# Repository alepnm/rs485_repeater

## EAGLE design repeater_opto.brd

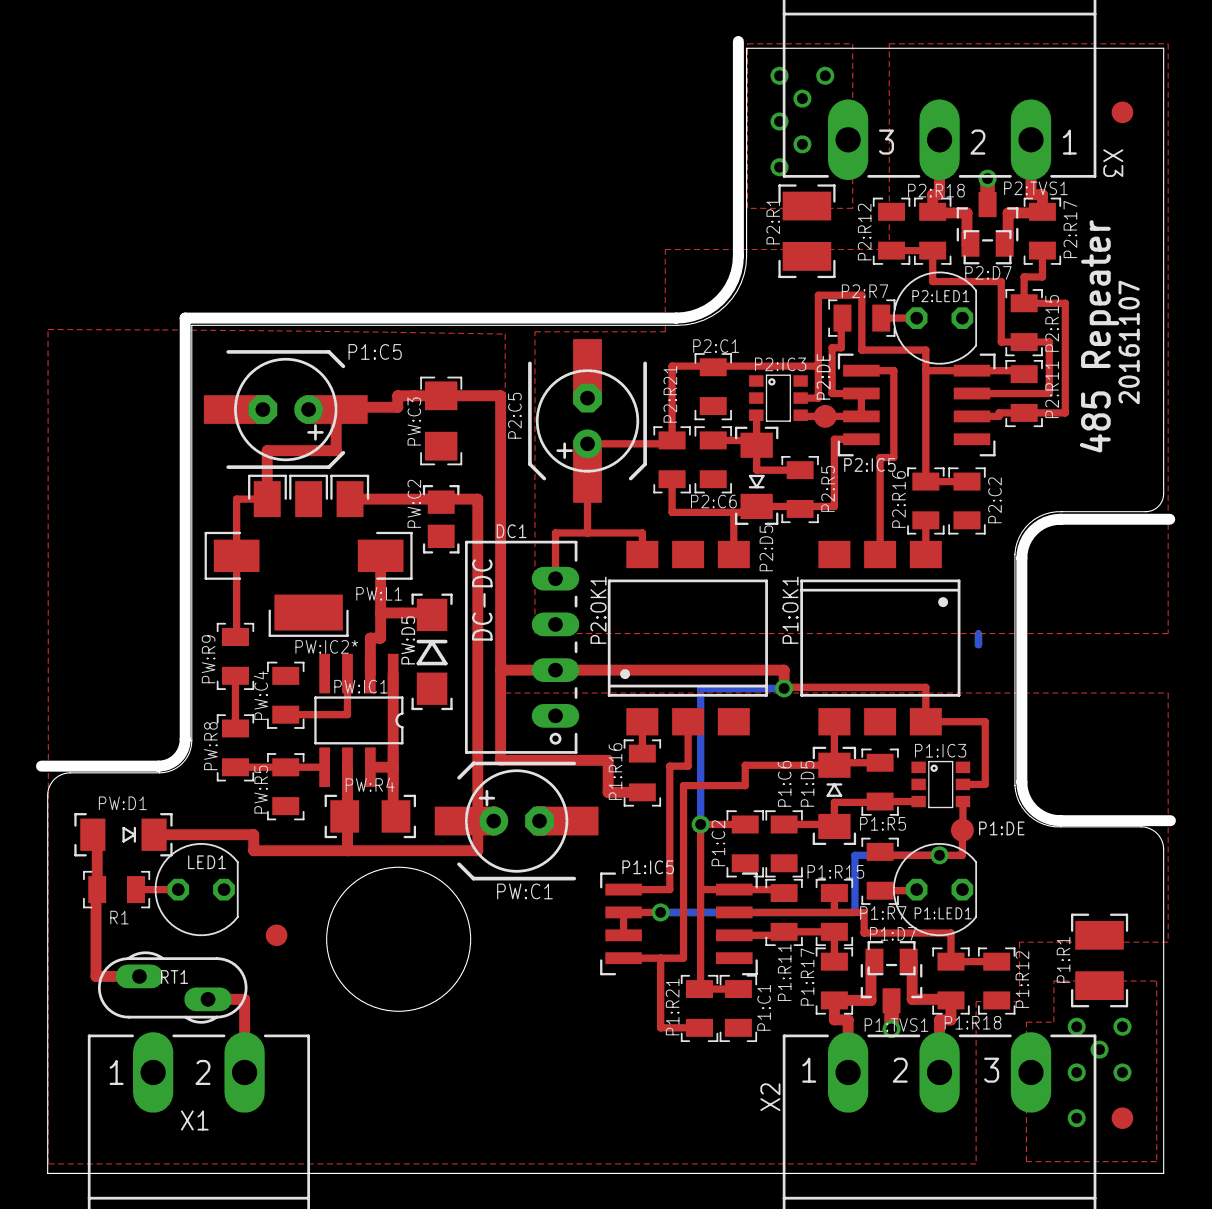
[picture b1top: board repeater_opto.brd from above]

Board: 2 copper layers, 62.7 x 62.6 mm, 69 parts (1 on the bottom side), 35 nets.

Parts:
DC1: 5V/5V; NME
LED1: Power; LED5MM
P1:C1, P1:C2, P1:C6, P2:C1, P2:C2, P2:C6: 0.1; C0805
P1:C5, P2:C5: 100x16V; SANYO-OSCON_SMD_C6
P1:C7, P2:C7: 100x16V; E2,5-6
P1:D5, P2:D5: BAS85; MINIMELF
P1:D7, P2:D7: PESD1LIN; SOD323-R
P1:DE, P2:DE: TPB1,27; B1,27
P1:IC3, P2:IC3: 74LVC2G14DBV; SOT23-6
P1:IC5, P2:IC5: MAX485CSA; ESOP-8
P1:LED1, P2:LED1: Link; LED5MM
P1:OK1, P2:OK1: H11L1MS; DIL6-SMD
P1:R1, P2:R1: 100; R1210
P1:R5, P1:R7, P2:R5, P2:R7: 10k; R0805
P1:R11, P1:R12, P2:R11, P2:R12: 4.7k; R0805
P1:R15, P2:R15: 120; R0805
P1:R16, P2:R16: 470; R0805
P1:R17, P1:R18, P2:R17, P2:R18: 10; R0805
P1:R21, P2:R21: 4k7; R0805
P1:TVS1, P2:TVS1: SM712; SOT23
PW:C1: 47x50V; SANYO-OSCON_SMD_C6
PW:C2: 10n; C0805
PW:C3: 1.0; C1206
PW:C4: 470; C0805
PW:C6: 47x50V; E2,5-6
PW:D1: BAS32; MINIMELF
PW:D5: 10MQ100; DO214BA
PW:IC1: MC34063AD; SO08
PW:IC2*: LM340-DCY; SOT223
PW:L1: 330uH; DR1030
PW:R4: 1.0; R1206
PW:R5: 4k7; R0805
PW:R8: 12k; R0805
PW:R9: 2k; R0805
R1: 4k7; R0805
RT1: 400mA; X40
SJ1: SJ
U$2: PLOKSTE_ISPJAUTA
X1: POWER; MSTBA2
X2: SIDE A; MSTBA3
X3: SIDE B; MSTBA3

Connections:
+24V: PW:D1.A, R1.1, RT1.2
GND1: DC1.1, LED1.K, P1:C1.2, P1:C2.2, P1:C5.-, P1:C6.2, P1:C7.-, P1:IC3.2, P1:IC5.5, P1:LED1.K, P1:OK1.5, P1:R1.1, P1:R12.1, PW:C1.-, PW:C2.2, PW:C3.2, PW:C4.2, PW:C6.-, PW:D5.A, PW:IC1.4, PW:IC2*.2, PW:IC2*.4, PW:R5.1, X1.1
GND2: DC1.3, P2:C1.2, P2:C2.2, P2:C5.-, P2:C6.2, P2:C7.-, P2:IC3.2, P2:IC5.5, P2:LED1.K, P2:OK1.5, P2:R1.1, P2:R12.1
unnamed: LED1.A, R1.2
unnamed: RT1.1, X1.2
unnamed: P1:R16.1, P2:OK1.1
unnamed: P1:IC5.1, P2:OK1.2
unnamed: P1:OK1.1, P2:R16.1
unnamed: P1:OK1.2, P2:IC5.1
P1:LED+: P1:DE.PP, P1:IC3.4, P1:IC5.2, P1:IC5.3, P1:R7.2
P1:N$1: P1:LED1.A, P1:R7.1
P1:N$2: P1:IC5.7, P1:R12.2, P1:R15.1, P1:R18.1
P1:N$3: P1:IC5.6, P1:R11.2, P1:R15.2, P1:R17.1
P1:N$7: P1:C6.1, P1:D5.A, P1:IC3.3, P1:R5.2
P1:RX: P1:D5.C, P1:IC5.4, P1:OK1.4, P1:R5.1, P1:R21.1
P2:LED+: P2:DE.PP, P2:IC3.4, P2:IC5.2, P2:IC5.3, P2:R7.2
P2:N$1: P2:LED1.A, P2:R7.1
P2:N$2: P2:IC5.7, P2:R12.2, P2:R15.1, P2:R18.1
P2:N$3: P2:IC5.6, P2:R11.2, P2:R15.2, P2:R17.1
P2:N$7: P2:C6.1, P2:D5.A, P2:IC3.3, P2:R5.2
P2:RX: P2:D5.C, P2:IC5.4, P2:OK1.4, P2:R5.1, P2:R21.1
PE1: P1:R1.2, P1:TVS1.3, SJ1.1, X2.3
PE2: P2:R1.2, P2:TVS1.3, SJ1.2, X3.3
PW:N$2: PW:C1.+, PW:C2.1, PW:C6.+, PW:D1.C, PW:IC1.6, PW:IC2*.1, PW:R4.1
PW:N$29: PW:IC1.1, PW:IC1.7, PW:IC1.8, PW:R4.2
PW:N$30: PW:C4.1, PW:IC1.3
PW:N$33: PW:R8.2, PW:R9.1
PW:N$34: PW:IC1.5, PW:R5.2, PW:R8.1
PW:N$35: PW:D5.C, PW:IC1.2, PW:L1.1
RS1A: P1:D7.C, P1:R17.2, P1:TVS1.2, X2.1
RS1B: P1:D7.A, P1:R18.2, P1:TVS1.1, X2.2
RS2A: P2:D7.C, P2:R17.2, P2:TVS1.2, X3.1
RS2B: P2:D7.A, P2:R18.2, P2:TVS1.1, X3.2
VCC1: DC1.2, P1:C1.1, P1:C2.1, P1:C5.+, P1:C7.+, P1:IC3.5, P1:IC5.8, P1:OK1.6, P1:R11.1, P1:R16.2, P1:R21.2, PW:C3.1, PW:IC2*.3, PW:L1.2, PW:R9.2
VCC2: DC1.4, P2:C1.1, P2:C2.1, P2:C5.+, P2:C7.+, P2:IC3.5, P2:IC5.8, P2:OK1.6, P2:R11.1, P2:R16.2, P2:R21.2

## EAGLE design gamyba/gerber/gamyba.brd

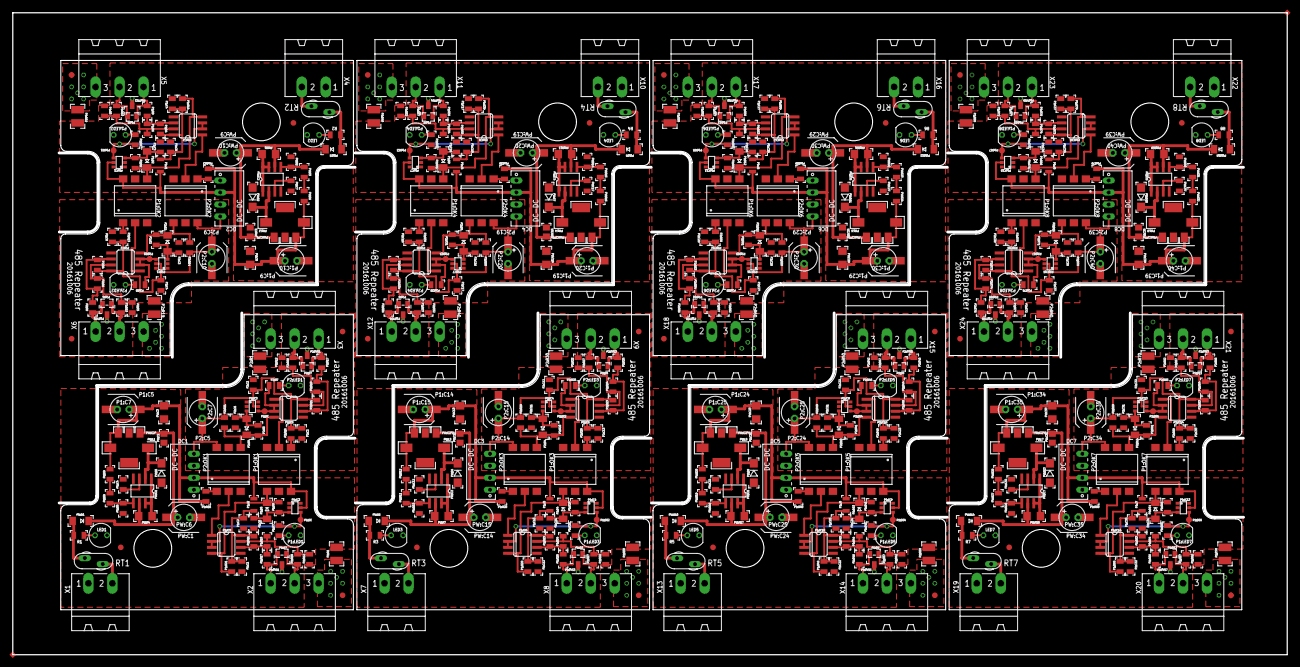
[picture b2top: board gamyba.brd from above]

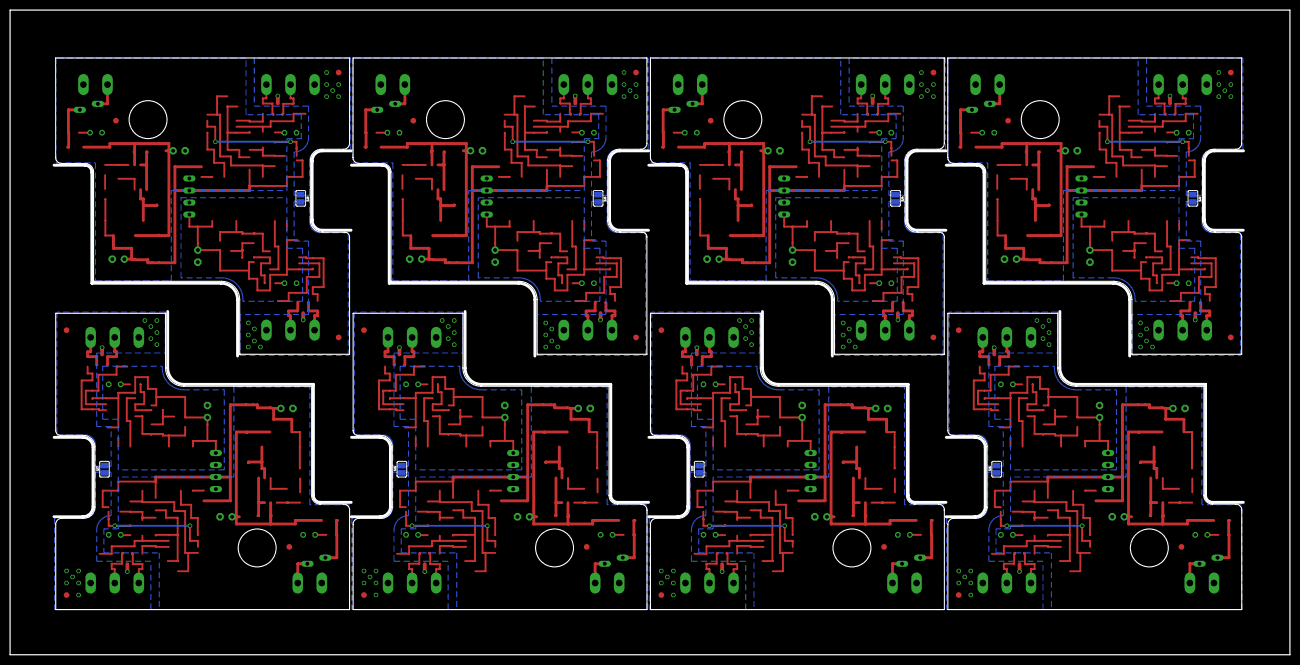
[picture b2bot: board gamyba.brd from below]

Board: 2 copper layers, 269.6 x 135.6 mm, 564 parts (8 on the bottom side), 280 nets.

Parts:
DC1, DC2, DC3, DC4, DC5, DC6, DC7, DC8: 5V/5V; NME
E$1, E$2, E$3, E$4: REF; TP2
LED1, LED2, LED3, LED4, LED5, LED6, LED7, LED8: Power; LED5MM
P1:C1, P1:C2, P1:C3, P1:C4, P1:C6, P1:C8, P1:C11, P1:C12, P1:C13, P1:C16, P1:C17, P1:C18, P1:C21, P1:C22, P1:C23, P1:C26, P1:C27, P1:C28, P1:C31, P1:C32, P1:C33, P1:C36, P1:C37, P1:C38, P2:C1, P2:C2, P2:C3, P2:C4, P2:C6, P2:C8, P2:C11, P2:C12, P2:C13, P2:C16, P2:C17, P2:C18, P2:C21, P2:C22, P2:C23, P2:C26, P2:C27, P2:C28, P2:C31, P2:C32, P2:C33, P2:C36, P2:C37, P2:C38: 0.1; C0805
P1:C5, P1:C9, P1:C14, P1:C19, P1:C24, P1:C29, P1:C34, P1:C39, P2:C5, P2:C9, P2:C14, P2:C19, P2:C24, P2:C29, P2:C34, P2:C39: 100x10V; SANYO-OSCON_SMD_C6
P1:C7, P1:C10, P1:C15, P1:C20, P1:C25, P1:C30, P1:C35, P1:C40, P2:C7, P2:C10, P2:C15, P2:C20, P2:C25, P2:C30, P2:C35, P2:C40: 100x10V; E2,5-6
P1:D1, P1:D3, P1:D6, P1:D7, P1:D9, P1:D11, P1:D13, P1:D15, P2:D1, P2:D3, P2:D6, P2:D7, P2:D9, P2:D11, P2:D13, P2:D15: PESD1LIN; SOD323-R
P1:D2, P1:D4, P1:D5, P1:D8, P1:D10, P1:D12, P1:D14, P1:D16, P2:D2, P2:D4, P2:D5, P2:D8, P2:D10, P2:D12, P2:D14, P2:D16: BAS85; MINIMELF
P1:DE, P1:DE1, P1:DE2, P1:DE3, P1:DE4, P1:DE5, P1:DE6, P1:DE7, P2:DE, P2:DE1, P2:DE2, P2:DE3, P2:DE4, P2:DE5, P2:DE6, P2:DE7: TPB1,27; B1,27
P1:IC1, P1:IC3, P1:IC4, P1:IC7, P1:IC9, P1:IC11, P1:IC13, P1:IC15, P2:IC1, P2:IC3, P2:IC4, P2:IC7, P2:IC9, P2:IC11, P2:IC13, P2:IC15: 74LVC2G14DBV; SOT23-6
P1:IC2, P1:IC5, P1:IC6, P1:IC8, P1:IC10, P1:IC12, P1:IC14, P1:IC16, P2:IC2, P2:IC5, P2:IC6, P2:IC8, P2:IC10, P2:IC12, P2:IC14, P2:IC16: MAX485CSA; SO08
P1:J1, P1:J2, P1:J3, P1:J4, P1:J5, P1:J6, P1:J7, P1:J8: 0; JUMPER_0805
P1:LED1, P1:LED2, P1:LED3, P1:LED4, P1:LED5, P1:LED6, P1:LED7, P1:LED8, P2:LED1, P2:LED2, P2:LED3, P2:LED4, P2:LED5, P2:LED6, P2:LED7, P2:LED8: Link; LED5MM
P1:OK1, P1:OK2, P1:OK3, P1:OK4, P1:OK5, P1:OK6, P1:OK7, P1:OK8, P2:OK1, P2:OK2, P2:OK3, P2:OK4, P2:OK5, P2:OK6, P2:OK7, P2:OK8: H11L1MS; DIL6-SMD
P1:R1, P1:R19, P1:R30, P1:R40, P1:R50, P1:R60, P1:R70, P1:R80, P2:R1, P2:R19, P2:R30, P2:R40, P2:R50, P2:R60, P2:R70, P2:R80: 101; R1210
P1:R2, P1:R5, P1:R7, P1:R8, P1:R20, P1:R25, P1:R31, P1:R35, P1:R41, P1:R45, P1:R51, P1:R55, P1:R61, P1:R65, P1:R71, P1:R75, P2:R2, P2:R5, P2:R7, P2:R8, P2:R20, P2:R25, P2:R31, P2:R35, P2:R41, P2:R45, P2:R51, P2:R55, P2:R61, P2:R65, P2:R71, P2:R75: 103; R0805
P1:R3, P1:R4, P1:R11, P1:R12, P1:R22, P1:R23, P1:R32, P1:R33, P1:R42, P1:R43, P1:R52, P1:R53, P1:R62, P1:R63, P1:R72, P1:R73, P2:R3, P2:R4, P2:R11, P2:R12, P2:R22, P2:R23, P2:R32, P2:R33, P2:R42, P2:R43, P2:R52, P2:R53, P2:R62, P2:R63, P2:R72, P2:R73: 202; R0805
P1:R6, P1:R15, P1:R24, P1:R34, P1:R44, P1:R54, P1:R64, P1:R74, P2:R6, P2:R15, P2:R24, P2:R34, P2:R44, P2:R54, P2:R64, P2:R74: 121; R0805
P1:R9, P1:R10, P1:R17, P1:R18, P1:R26, P1:R27, P1:R36, P1:R37, P1:R46, P1:R47, P1:R56, P1:R57, P1:R66, P1:R67, P1:R76, P1:R77, P2:R9, P2:R10, P2:R17, P2:R18, P2:R26, P2:R27, P2:R36, P2:R37, P2:R46, P2:R47, P2:R56, P2:R57, P2:R66, P2:R67, P2:R76, P2:R77: 100; R0805
P1:R13, P1:R16, P1:R28, P1:R38, P1:R48, P1:R58, P1:R68, P1:R78, P2:R13, P2:R16, P2:R28, P2:R38, P2:R48, P2:R58, P2:R68, P2:R78: 471; R0805
P1:R14, P1:R21, P1:R29, P1:R39, P1:R49, P1:R59, P1:R69, P1:R79, P2:R14, P2:R21, P2:R29, P2:R39, P2:R49, P2:R59, P2:R69, P2:R79: 472; R0805
P1:TVS1, P1:TVS2, P1:TVS3, P1:TVS4, P1:TVS5, P1:TVS6, P1:TVS7, P1:TVS8, P2:TVS1, P2:TVS2, P2:TVS3, P2:TVS4, P2:TVS5, P2:TVS6, P2:TVS7, P2:TVS8: SM712; SOT23
PW:C1, PW:C9, PW:C14, PW:C19, PW:C24, PW:C29, PW:C34, PW:C39: 47x35V; SANYO-OSCON_SMD_C6
PW:C2, PW:C5, PW:C11, PW:C16, PW:C21, PW:C26, PW:C31, PW:C36: 10n; C0805
PW:C3, PW:C8, PW:C13, PW:C18, PW:C23, PW:C28, PW:C33, PW:C38: 1.0; C1206
PW:C4, PW:C7, PW:C12, PW:C17, PW:C22, PW:C27, PW:C32, PW:C37: 470; C0805
PW:C6, PW:C10, PW:C15, PW:C20, PW:C25, PW:C30, PW:C35, PW:C40: 47x35V; E2,5-6
PW:D1, PW:D3, PW:D6, PW:D8, PW:D10, PW:D12, PW:D14, PW:D16: LL4148; MINIMELF
PW:D2, PW:D4, PW:D5, PW:D7, PW:D9, PW:D11, PW:D13, PW:D15: 10MQ100; DO214BA
PW:IC1, PW:IC2, PW:IC3, PW:IC4, PW:IC5, PW:IC6, PW:IC7, PW:IC8: MC34063AD; SO08
PW:IC2*, PW:IC2*1, PW:IC2*2, PW:IC2*3, PW:IC2*4, PW:IC2*5, PW:IC2*6, PW:IC2*7: LM340-DCY; SOT223
PW:L1, PW:L2, PW:L3, PW:L4, PW:L5, PW:L6, PW:L7, PW:L8: 330uH; DR1030
PW:R1, PW:R4, PW:R7, PW:R13, PW:R17, PW:R21, PW:R25, PW:R29: 1.0; R1206
PW:R2, PW:R5, PW:R10, PW:R14, PW:R18, PW:R22, PW:R26, PW:R30: 472; R0805
PW:R3, PW:R8, PW:R11, PW:R15, PW:R19, PW:R23, PW:R27, PW:R31: 123; R0805
PW:R6, PW:R9, PW:R12, PW:R16, PW:R20, PW:R24, PW:R28, PW:R32: 202; R0805
R1, R2, R3, R4, R5, R6, R7, R8: 472; R0805
RT1, RT2, RT3, RT4, RT5, RT6, RT7, RT8: 100mA; X40
SJ1, SJ2, SJ3, SJ4, SJ5, SJ6, SJ7, SJ8: SJ
U$1, U$2, U$3, U$4, U$5, U$6, U$7, U$8: PLOKSTE_ISPJAUTA
X1, X4, X7, X10, X13, X16, X19, X22: POWER; MSTBA2
X2, X5, X8, X11, X14, X17, X20, X23: RS1; MSTBA3
X3, X6, X9, X12, X15, X18, X21, X24: RS2; MSTBA3

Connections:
+24V: PW:D1.A, R1.1, RT1.2
+24V1: PW:D3.A, R2.1, RT2.2
+24V2: PW:D6.A, R3.1, RT3.2
+24V3: PW:D8.A, R4.1, RT4.2
+24V4: PW:D10.A, R5.1, RT5.2
+24V5: PW:D12.A, R6.1, RT6.2
+24V6: PW:D14.A, R7.1, RT7.2
+24V7: PW:D16.A, R8.1, RT8.2
GND1: DC1.1, LED1.K, P1:C1.2, P1:C2.2, P1:C5.-, P1:C6.2, P1:C7.-, P1:IC3.2, P1:IC5.5, P1:LED1.K, P1:OK1.5, P1:R1.1, P1:R12.1, PW:C1.-, PW:C2.2, PW:C3.2, PW:C4.2, PW:C6.-, PW:D5.A, PW:IC1.4, PW:IC2*.2, PW:IC2*.4, PW:R5.1, X1.1
GND2: DC1.3, P2:C1.2, P2:C2.2, P2:C5.-, P2:C6.2, P2:C7.-, P2:IC3.2, P2:IC5.5, P2:LED1.K, P2:OK1.5, P2:R1.1, P2:R12.1
GND3: DC2.3, P2:C3.2, P2:C4.2, P2:C8.2, P2:C9.-, P2:C10.-, P2:IC1.2, P2:IC2.5, P2:LED2.K, P2:OK2.5, P2:R3.1, P2:R19.1
GND4: DC2.1, LED2.K, P1:C3.2, P1:C4.2, P1:C8.2, P1:C9.-, P1:C10.-, P1:IC1.2, P1:IC2.5, P1:LED2.K, P1:OK2.5, P1:R3.1, P1:R19.1, PW:C5.2, PW:C7.2, PW:C8.2, PW:C9.-, PW:C10.-, PW:D2.A, PW:IC2.4, PW:IC2*1.2, PW:IC2*1.4, PW:R2.1, X4.1
GND5: DC3.3, P2:C11.2, P2:C12.2, P2:C13.2, P2:C14.-, P2:C15.-, P2:IC4.2, P2:IC6.5, P2:LED3.K, P2:OK3.5, P2:R22.1, P2:R30.1
GND6: DC3.1, LED3.K, P1:C11.2, P1:C12.2, P1:C13.2, P1:C14.-, P1:C15.-, P1:IC4.2, P1:IC6.5, P1:LED3.K, P1:OK3.5, P1:R22.1, P1:R30.1, PW:C11.2, PW:C12.2, PW:C13.2, PW:C14.-, PW:C15.-, PW:D4.A, PW:IC2*2.2, PW:IC2*2.4, PW:IC3.4, PW:R10.1, X7.1
GND7: DC4.3, P2:C16.2, P2:C17.2, P2:C18.2, P2:C19.-, P2:C20.-, P2:IC7.2, P2:IC8.5, P2:LED4.K, P2:OK4.5, P2:R32.1, P2:R40.1
GND8: DC4.1, LED4.K, P1:C16.2, P1:C17.2, P1:C18.2, P1:C19.-, P1:C20.-, P1:IC7.2, P1:IC8.5, P1:LED4.K, P1:OK4.5, P1:R32.1, P1:R40.1, PW:C16.2, PW:C17.2, PW:C18.2, PW:C19.-, PW:C20.-, PW:D7.A, PW:IC2*3.2, PW:IC2*3.4, PW:IC4.4, PW:R14.1, X10.1
GND9: DC5.3, P2:C21.2, P2:C22.2, P2:C23.2, P2:C24.-, P2:C25.-, P2:IC9.2, P2:IC10.5, P2:LED5.K, P2:OK5.5, P2:R42.1, P2:R50.1
GND10: DC5.1, LED5.K, P1:C21.2, P1:C22.2, P1:C23.2, P1:C24.-, P1:C25.-, P1:IC9.2, P1:IC10.5, P1:LED5.K, P1:OK5.5, P1:R42.1, P1:R50.1, PW:C21.2, PW:C22.2, PW:C23.2, PW:C24.-, PW:C25.-, PW:D9.A, PW:IC2*4.2, PW:IC2*4.4, PW:IC5.4, PW:R18.1, X13.1
GND11: DC6.3, P2:C26.2, P2:C27.2, P2:C28.2, P2:C29.-, P2:C30.-, P2:IC11.2, P2:IC12.5, P2:LED6.K, P2:OK6.5, P2:R52.1, P2:R60.1
GND12: DC6.1, LED6.K, P1:C26.2, P1:C27.2, P1:C28.2, P1:C29.-, P1:C30.-, P1:IC11.2, P1:IC12.5, P1:LED6.K, P1:OK6.5, P1:R52.1, P1:R60.1, PW:C26.2, PW:C27.2, PW:C28.2, PW:C29.-, PW:C30.-, PW:D11.A, PW:IC2*5.2, PW:IC2*5.4, PW:IC6.4, PW:R22.1, X16.1
GND13: DC7.3, P2:C31.2, P2:C32.2, P2:C33.2, P2:C34.-, P2:C35.-, P2:IC13.2, P2:IC14.5, P2:LED7.K, P2:OK7.5, P2:R62.1, P2:R70.1
GND14: DC7.1, LED7.K, P1:C31.2, P1:C32.2, P1:C33.2, P1:C34.-, P1:C35.-, P1:IC13.2, P1:IC14.5, P1:LED7.K, P1:OK7.5, P1:R62.1, P1:R70.1, PW:C31.2, PW:C32.2, PW:C33.2, PW:C34.-, PW:C35.-, PW:D13.A, PW:IC2*6.2, PW:IC2*6.4, PW:IC7.4, PW:R26.1, X19.1
GND15: DC8.3, P2:C36.2, P2:C37.2, P2:C38.2, P2:C39.-, P2:C40.-, P2:IC15.2, P2:IC16.5, P2:LED8.K, P2:OK8.5, P2:R72.1, P2:R80.1
GND16: DC8.1, LED8.K, P1:C36.2, P1:C37.2, P1:C38.2, P1:C39.-, P1:C40.-, P1:IC15.2, P1:IC16.5, P1:LED8.K, P1:OK8.5, P1:R72.1, P1:R80.1, PW:C36.2, PW:C37.2, PW:C38.2, PW:C39.-, PW:C40.-, PW:D15.A, PW:IC2*7.2, PW:IC2*7.4, PW:IC8.4, PW:R30.1, X22.1
unnamed: LED1.A, R1.2
unnamed: RT1.1, X1.2
unnamed: P1:R13.1, P2:OK2.1
unnamed: P1:OK2.1, P2:R13.1
unnamed: P1:IC2.1, P2:OK2.2
unnamed: P1:OK2.2, P2:IC2.1
unnamed: RT2.1, X4.2
unnamed: LED2.A, R2.2
unnamed: P1:R28.1, P2:OK3.1
unnamed: P1:OK3.1, P2:R28.1
unnamed: P1:IC6.1, P2:OK3.2
unnamed: P1:R16.1, P2:OK1.1
unnamed: P1:IC5.1, P2:OK1.2
unnamed: P1:OK1.1, P2:R16.1
unnamed: P1:OK1.2, P2:IC5.1
unnamed: P1:OK3.2, P2:IC6.1
unnamed: RT3.1, X7.2
unnamed: LED3.A, R3.2
unnamed: P1:R38.1, P2:OK4.1
unnamed: P1:OK4.1, P2:R38.1
unnamed: P1:IC8.1, P2:OK4.2
unnamed: P1:OK4.2, P2:IC8.1
unnamed: RT4.1, X10.2
unnamed: LED4.A, R4.2
unnamed: P1:R48.1, P2:OK5.1
unnamed: P1:OK5.1, P2:R48.1
unnamed: P1:IC10.1, P2:OK5.2
unnamed: P1:OK5.2, P2:IC10.1
unnamed: RT5.1, X13.2
unnamed: LED5.A, R5.2
unnamed: P1:R58.1, P2:OK6.1
unnamed: P1:OK6.1, P2:R58.1
unnamed: P1:IC12.1, P2:OK6.2
unnamed: P1:OK6.2, P2:IC12.1
unnamed: RT6.1, X16.2
unnamed: LED6.A, R6.2
unnamed: P1:R68.1, P2:OK7.1
unnamed: P1:OK7.1, P2:R68.1
unnamed: P1:IC14.1, P2:OK7.2
unnamed: P1:OK7.2, P2:IC14.1
unnamed: RT7.1, X19.2
unnamed: LED7.A, R7.2
unnamed: P1:R78.1, P2:OK8.1
unnamed: P1:OK8.1, P2:R78.1
unnamed: P1:IC16.1, P2:OK8.2
unnamed: P1:OK8.2, P2:IC16.1
unnamed: RT8.1, X22.2
unnamed: LED8.A, R8.2
P1:LED+: P1:DE.PP, P1:IC3.4, P1:IC5.2, P1:IC5.3, P1:R7.2
P1:LED+1: P1:DE1.PP, P1:IC1.4, P1:IC2.2, P1:IC2.3, P1:R8.2
P1:LED+2: P1:DE2.PP, P1:IC4.4, P1:IC6.2, P1:IC6.3, P1:R25.2
P1:LED+3: P1:DE3.PP, P1:IC7.4, P1:IC8.2, P1:IC8.3, P1:R35.2
P1:LED+4: P1:DE4.PP, P1:IC9.4, P1:IC10.2, P1:IC10.3, P1:R45.2
P1:LED+5: P1:DE5.PP, P1:IC11.4, P1:IC12.2, P1:IC12.3, P1:R55.2
P1:LED+6: P1:DE6.PP, P1:IC13.4, P1:IC14.2, P1:IC14.3, P1:R65.2
P1:LED+7: P1:DE7.PP, P1:IC15.4, P1:IC16.2, P1:IC16.3, P1:R75.2
P1:N$1: P1:LED1.A, P1:R7.1
P1:N$2: P1:IC5.7, P1:R12.2, P1:R15.1, P1:R18.1
P1:N$3: P1:IC5.6, P1:R11.2, P1:R15.2, P1:R17.1
P1:N$4: P1:C3.1, P1:D2.A, P1:IC1.3, P1:R2.2
P1:N$5: P1:IC2.7, P1:R3.2, P1:R6.1, P1:R10.1
P1:N$6: P1:IC2.6, P1:R4.2, P1:R6.2, P1:R9.1
P1:N$7: P1:C6.1, P1:D5.A, P1:IC3.3, P1:R5.2
P1:N$8: P1:LED2.A, P1:R8.1
P1:N$9: P1:C11.1, P1:D4.A, P1:IC4.3, P1:R20.2
P1:N$10: P1:IC6.7, P1:R22.2, P1:R24.1, P1:R27.1
P1:N$11: P1:IC6.6, P1:R23.2, P1:R24.2, P1:R26.1
P1:N$12: P1:LED3.A, P1:R25.1
P1:N$13: P1:C16.1, P1:D8.A, P1:IC7.3, P1:R31.2
P1:N$14: P1:IC8.7, P1:R32.2, P1:R34.1, P1:R37.1
P1:N$15: P1:IC8.6, P1:R33.2, P1:R34.2, P1:R36.1
P1:N$16: P1:LED4.A, P1:R35.1
P1:N$17: P1:C21.1, P1:D10.A, P1:IC9.3, P1:R41.2
P1:N$18: P1:IC10.7, P1:R42.2, P1:R44.1, P1:R47.1
P1:N$19: P1:IC10.6, P1:R43.2, P1:R44.2, P1:R46.1
P1:N$20: P1:LED5.A, P1:R45.1
P1:N$21: P1:C26.1, P1:D12.A, P1:IC11.3, P1:R51.2
P1:N$22: P1:IC12.7, P1:R52.2, P1:R54.1, P1:R57.1
P1:N$23: P1:IC12.6, P1:R53.2, P1:R54.2, P1:R56.1
P1:N$24: P1:LED6.A, P1:R55.1
P1:N$25: P1:C31.1, P1:D14.A, P1:IC13.3, P1:R61.2
P1:N$26: P1:IC14.7, P1:R62.2, P1:R64.1, P1:R67.1
P1:N$27: P1:IC14.6, P1:R63.2, P1:R64.2, P1:R66.1
P1:N$28: P1:LED7.A, P1:R65.1
P1:N$29: P1:C36.1, P1:D16.A, P1:IC15.3, P1:R71.2
P1:N$30: P1:IC16.7, P1:R72.2, P1:R74.1, P1:R77.1
P1:N$31: P1:IC16.6, P1:R73.2, P1:R74.2, P1:R76.1
P1:N$32: P1:LED8.A, P1:R75.1
P1:RX: P1:D5.C, P1:IC5.4, P1:OK1.4, P1:R5.1, P1:R21.1
P1:RX1: P1:D2.C, P1:IC2.4, P1:OK2.4, P1:R2.1, P1:R14.1
P1:RX2: P1:D4.C, P1:IC6.4, P1:OK3.4, P1:R20.1, P1:R29.1
P1:RX3: P1:D8.C, P1:IC8.4, P1:OK4.4, P1:R31.1, P1:R39.1
P1:RX4: P1:D10.C, P1:IC10.4, P1:OK5.4, P1:R41.1, P1:R49.1
P1:RX5: P1:D12.C, P1:IC12.4, P1:OK6.4, P1:R51.1, P1:R59.1
P1:RX6: P1:D14.C, P1:IC14.4, P1:OK7.4, P1:R61.1, P1:R69.1
P1:RX7: P1:D16.C, P1:IC16.4, P1:OK8.4, P1:R71.1, P1:R79.1
P2:LED+: P2:DE.PP, P2:IC3.4, P2:IC5.2, P2:IC5.3, P2:R7.2
P2:LED+1: P2:DE1.PP, P2:IC1.4, P2:IC2.2, P2:IC2.3, P2:R8.2
P2:LED+2: P2:DE2.PP, P2:IC4.4, P2:IC6.2, P2:IC6.3, P2:R25.2
P2:LED+3: P2:DE3.PP, P2:IC7.4, P2:IC8.2, P2:IC8.3, P2:R35.2
P2:LED+4: P2:DE4.PP, P2:IC9.4, P2:IC10.2, P2:IC10.3, P2:R45.2
P2:LED+5: P2:DE5.PP, P2:IC11.4, P2:IC12.2, P2:IC12.3, P2:R55.2
P2:LED+6: P2:DE6.PP, P2:IC13.4, P2:IC14.2, P2:IC14.3, P2:R65.2
P2:LED+7: P2:DE7.PP, P2:IC15.4, P2:IC16.2, P2:IC16.3, P2:R75.2
P2:N$1: P2:LED1.A, P2:R7.1
P2:N$2: P2:IC5.7, P2:R12.2, P2:R15.1, P2:R18.1
P2:N$3: P2:IC5.6, P2:R11.2, P2:R15.2, P2:R17.1
P2:N$4: P2:C3.1, P2:D2.A, P2:IC1.3, P2:R2.2
P2:N$5: P2:IC2.7, P2:R3.2, P2:R6.1, P2:R10.1
P2:N$6: P2:IC2.6, P2:R4.2, P2:R6.2, P2:R9.1
P2:N$7: P2:C6.1, P2:D5.A, P2:IC3.3, P2:R5.2
P2:N$8: P2:LED2.A, P2:R8.1
P2:N$9: P2:C11.1, P2:D4.A, P2:IC4.3, P2:R20.2
P2:N$10: P2:IC6.7, P2:R22.2, P2:R24.1, P2:R27.1
P2:N$11: P2:IC6.6, P2:R23.2, P2:R24.2, P2:R26.1
P2:N$12: P2:LED3.A, P2:R25.1
P2:N$13: P2:C16.1, P2:D8.A, P2:IC7.3, P2:R31.2
P2:N$14: P2:IC8.7, P2:R32.2, P2:R34.1, P2:R37.1
P2:N$15: P2:IC8.6, P2:R33.2, P2:R34.2, P2:R36.1
P2:N$16: P2:LED4.A, P2:R35.1
P2:N$17: P2:C21.1, P2:D10.A, P2:IC9.3, P2:R41.2
P2:N$18: P2:IC10.7, P2:R42.2, P2:R44.1, P2:R47.1
P2:N$19: P2:IC10.6, P2:R43.2, P2:R44.2, P2:R46.1
P2:N$20: P2:LED5.A, P2:R45.1
P2:N$21: P2:C26.1, P2:D12.A, P2:IC11.3, P2:R51.2
P2:N$22: P2:IC12.7, P2:R52.2, P2:R54.1, P2:R57.1
P2:N$23: P2:IC12.6, P2:R53.2, P2:R54.2, P2:R56.1
P2:N$24: P2:LED6.A, P2:R55.1
P2:N$25: P2:C31.1, P2:D14.A, P2:IC13.3, P2:R61.2
P2:N$26: P2:IC14.7, P2:R62.2, P2:R64.1, P2:R67.1
P2:N$27: P2:IC14.6, P2:R63.2, P2:R64.2, P2:R66.1
P2:N$28: P2:LED7.A, P2:R65.1
P2:N$29: P2:C36.1, P2:D16.A, P2:IC15.3, P2:R71.2
P2:N$30: P2:IC16.7, P2:R72.2, P2:R74.1, P2:R77.1
P2:N$31: P2:IC16.6, P2:R73.2, P2:R74.2, P2:R76.1
P2:N$32: P2:LED8.A, P2:R75.1
P2:RX: P2:D5.C, P2:IC5.4, P2:OK1.4, P2:R5.1, P2:R21.1
P2:RX1: P2:D2.C, P2:IC2.4, P2:OK2.4, P2:R2.1, P2:R14.1
P2:RX2: P2:D4.C, P2:IC6.4, P2:OK3.4, P2:R20.1, P2:R29.1
P2:RX3: P2:D8.C, P2:IC8.4, P2:OK4.4, P2:R31.1, P2:R39.1
P2:RX4: P2:D10.C, P2:IC10.4, P2:OK5.4, P2:R41.1, P2:R49.1
P2:RX5: P2:D12.C, P2:IC12.4, P2:OK6.4, P2:R51.1, P2:R59.1
P2:RX6: P2:D14.C, P2:IC14.4, P2:OK7.4, P2:R61.1, P2:R69.1
P2:RX7: P2:D16.C, P2:IC16.4, P2:OK8.4, P2:R71.1, P2:R79.1
PE1: P1:R1.2, P1:TVS1.3, SJ1.1, X2.3
PE2: P2:R1.2, P2:TVS1.3, SJ1.2, X3.3
PE3: P1:R19.2, P1:TVS2.3, SJ2.1, X5.3
PE4: P2:R19.2, P2:TVS2.3, SJ2.2, X6.3
PE5: P1:R30.2, P1:TVS3.3, SJ3.1, X8.3
PE6: P2:R30.2, P2:TVS3.3, SJ3.2, X9.3
PE7: P1:R40.2, P1:TVS4.3, SJ4.1, X11.3
PE8: P2:R40.2, P2:TVS4.3, SJ4.2, X12.3
PE9: P1:R50.2, P1:TVS5.3, SJ5.1, X14.3
PE10: P2:R50.2, P2:TVS5.3, SJ5.2, X15.3
PE11: P1:R60.2, P1:TVS6.3, SJ6.1, X17.3
PE12: P2:R60.2, P2:TVS6.3, SJ6.2, X18.3
PE13: P1:R70.2, P1:TVS7.3, SJ7.1, X20.3
PE14: P2:R70.2, P2:TVS7.3, SJ7.2, X21.3
PE15: P1:R80.2, P1:TVS8.3, SJ8.1, X23.3
PE16: P2:R80.2, P2:TVS8.3, SJ8.2, X24.3
PW:N$1: PW:IC2.1, PW:IC2.7, PW:IC2.8, PW:R1.2
PW:N$2: PW:C1.+, PW:C2.1, PW:C6.+, PW:D1.C, PW:IC1.6, PW:IC2*.1, PW:R4.1
PW:N$3: PW:IC2.5, PW:R2.2, PW:R3.1
PW:N$4: PW:C7.1, PW:IC2.3
PW:N$5: PW:D2.C, PW:IC2.2, PW:L2.1
PW:N$6: PW:R3.2, PW:R6.1
PW:N$7: PW:C5.1, PW:C9.+, PW:C10.+, PW:D3.C, PW:IC2.6, PW:IC2*1.1, PW:R1.1
PW:N$8: PW:IC3.1, PW:IC3.7, PW:IC3.8, PW:R7.2
PW:N$9: PW:IC3.5, PW:R10.2, PW:R11.1
PW:N$10: PW:C12.1, PW:IC3.3
PW:N$11: PW:D4.C, PW:IC3.2, PW:L3.1
PW:N$12: PW:R11.2, PW:R12.1
PW:N$13: PW:C11.1, PW:C14.+, PW:C15.+, PW:D6.C, PW:IC2*2.1, PW:IC3.6, PW:R7.1
PW:N$14: PW:IC4.1, PW:IC4.7, PW:IC4.8, PW:R13.2
PW:N$15: PW:IC4.5, PW:R14.2, PW:R15.1
PW:N$16: PW:C17.1, PW:IC4.3
PW:N$17: PW:D7.C, PW:IC4.2, PW:L4.1
PW:N$18: PW:R15.2, PW:R16.1
PW:N$19: PW:C16.1, PW:C19.+, PW:C20.+, PW:D8.C, PW:IC2*3.1, PW:IC4.6, PW:R13.1
PW:N$20: PW:IC5.1, PW:IC5.7, PW:IC5.8, PW:R17.2
PW:N$21: PW:IC5.5, PW:R18.2, PW:R19.1
PW:N$22: PW:C22.1, PW:IC5.3
PW:N$23: PW:D9.C, PW:IC5.2, PW:L5.1
PW:N$24: PW:R19.2, PW:R20.1
PW:N$25: PW:C21.1, PW:C24.+, PW:C25.+, PW:D10.C, PW:IC2*4.1, PW:IC5.6, PW:R17.1
PW:N$26: PW:IC6.1, PW:IC6.7, PW:IC6.8, PW:R21.2
PW:N$27: PW:IC6.5, PW:R22.2, PW:R23.1
PW:N$28: PW:C27.1, PW:IC6.3
PW:N$29: PW:IC1.1, PW:IC1.7, PW:IC1.8, PW:R4.2
PW:N$30: PW:C4.1, PW:IC1.3
PW:N$31: PW:D11.C, PW:IC6.2, PW:L6.1
PW:N$32: PW:R23.2, PW:R24.1
PW:N$33: PW:R8.2, PW:R9.1
PW:N$34: PW:IC1.5, PW:R5.2, PW:R8.1
PW:N$35: PW:D5.C, PW:IC1.2, PW:L1.1
PW:N$36: PW:C26.1, PW:C29.+, PW:C30.+, PW:D12.C, PW:IC2*5.1, PW:IC6.6, PW:R21.1
PW:N$37: PW:IC7.1, PW:IC7.7, PW:IC7.8, PW:R25.2
PW:N$38: PW:IC7.5, PW:R26.2, PW:R27.1
PW:N$39: PW:C32.1, PW:IC7.3
PW:N$40: PW:D13.C, PW:IC7.2, PW:L7.1
PW:N$41: PW:R27.2, PW:R28.1
PW:N$42: PW:C31.1, PW:C34.+, PW:C35.+, PW:D14.C, PW:IC2*6.1, PW:IC7.6, PW:R25.1
PW:N$43: PW:IC8.1, PW:IC8.7, PW:IC8.8, PW:R29.2
PW:N$44: PW:IC8.5, PW:R30.2, PW:R31.1
PW:N$45: PW:C37.1, PW:IC8.3
PW:N$46: PW:D15.C, PW:IC8.2, PW:L8.1
PW:N$47: PW:R31.2, PW:R32.1
PW:N$48: PW:C36.1, PW:C39.+, PW:C40.+, PW:D16.C, PW:IC2*7.1, PW:IC8.6, PW:R29.1
RS1A: P1:D7.C, P1:R17.2, P1:TVS1.2, X2.1
RS1A1: P1:D1.C, P1:R9.2, P1:TVS2.2, X5.1
RS1A2: P1:D3.C, P1:R26.2, P1:TVS3.2, X8.1
RS1A3: P1:D6.C, P1:R36.2, P1:TVS4.2, X11.1
RS1A4: P1:D9.C, P1:R46.2, P1:TVS5.2, X14.1
RS1A5: P1:D11.C, P1:R56.2, P1:TVS6.2, X17.1
RS1A6: P1:D13.C, P1:R66.2, P1:TVS7.2, X20.1
RS1A7: P1:D15.C, P1:R76.2, P1:TVS8.2, X23.1
RS1B: P1:D7.A, P1:R18.2, P1:TVS1.1, X2.2
RS1B1: P1:D1.A, P1:R10.2, P1:TVS2.1, X5.2
RS1B2: P1:D3.A, P1:R27.2, P1:TVS3.1, X8.2
RS1B3: P1:D6.A, P1:R37.2, P1:TVS4.1, X11.2
RS1B4: P1:D9.A, P1:R47.2, P1:TVS5.1, X14.2
RS1B5: P1:D11.A, P1:R57.2, P1:TVS6.1, X17.2
RS1B6: P1:D13.A, P1:R67.2, P1:TVS7.1, X20.2
RS1B7: P1:D15.A, P1:R77.2, P1:TVS8.1, X23.2
RS2A: P2:D7.C, P2:R17.2, P2:TVS1.2, X3.1
RS2A1: P2:D1.C, P2:R9.2, P2:TVS2.2, X6.1
RS2A2: P2:D3.C, P2:R26.2, P2:TVS3.2, X9.1
RS2A3: P2:D6.C, P2:R36.2, P2:TVS4.2, X12.1
RS2A4: P2:D9.C, P2:R46.2, P2:TVS5.2, X15.1
RS2A5: P2:D11.C, P2:R56.2, P2:TVS6.2, X18.1
RS2A6: P2:D13.C, P2:R66.2, P2:TVS7.2, X21.1
RS2A7: P2:D15.C, P2:R76.2, P2:TVS8.2, X24.1
RS2B: P2:D7.A, P2:R18.2, P2:TVS1.1, X3.2
RS2B1: P2:D1.A, P2:R10.2, P2:TVS2.1, X6.2
RS2B2: P2:D3.A, P2:R27.2, P2:TVS3.1, X9.2
RS2B3: P2:D6.A, P2:R37.2, P2:TVS4.1, X12.2
RS2B4: P2:D9.A, P2:R47.2, P2:TVS5.1, X15.2
RS2B5: P2:D11.A, P2:R57.2, P2:TVS6.1, X18.2
RS2B6: P2:D13.A, P2:R67.2, P2:TVS7.1, X21.2
RS2B7: P2:D15.A, P2:R77.2, P2:TVS8.1, X24.2
VCC1: DC1.2, P1:C1.1, P1:C2.1, P1:C5.+, P1:C7.+, P1:IC3.5, P1:IC5.8, P1:J2.1, P1:J2.2, P1:OK1.6, P1:R11.1, P1:R16.2, P1:R21.2, PW:C3.1, PW:IC2*.3, PW:L1.2, PW:R9.2
VCC2: DC1.4, P2:C1.1, P2:C2.1, P2:C5.+, P2:C7.+, P2:IC3.5, P2:IC5.8, P2:OK1.6, P2:R11.1, P2:R16.2, P2:R21.2
VCC3: DC2.2, P1:C4.1, P1:C8.1, P1:C9.+, P1:C10.+, P1:IC1.5, P1:IC2.8, P1:J1.1, P1:J1.2, P1:OK2.6, P1:R4.1, P1:R13.2, P1:R14.2, PW:C8.1, PW:IC2*1.3, PW:L2.2, PW:R6.2
VCC4: DC2.4, P2:C4.1, P2:C8.1, P2:C9.+, P2:C10.+, P2:IC1.5, P2:IC2.8, P2:OK2.6, P2:R4.1, P2:R13.2, P2:R14.2
VCC5: DC3.2, P1:C12.1, P1:C13.1, P1:C14.+, P1:C15.+, P1:IC4.5, P1:IC6.8, P1:J3.1, P1:J3.2, P1:OK3.6, P1:R23.1, P1:R28.2, P1:R29.2, PW:C13.1, PW:IC2*2.3, PW:L3.2, PW:R12.2
VCC6: DC3.4, P2:C12.1, P2:C13.1, P2:C14.+, P2:C15.+, P2:IC4.5, P2:IC6.8, P2:OK3.6, P2:R23.1, P2:R28.2, P2:R29.2
VCC7: DC4.2, P1:C17.1, P1:C18.1, P1:C19.+, P1:C20.+, P1:IC7.5, P1:IC8.8, P1:J4.1, P1:J4.2, P1:OK4.6, P1:R33.1, P1:R38.2, P1:R39.2, PW:C18.1, PW:IC2*3.3, PW:L4.2, PW:R16.2
VCC8: DC4.4, P2:C17.1, P2:C18.1, P2:C19.+, P2:C20.+, P2:IC7.5, P2:IC8.8, P2:OK4.6, P2:R33.1, P2:R38.2, P2:R39.2
VCC9: DC5.2, P1:C22.1, P1:C23.1, P1:C24.+, P1:C25.+, P1:IC9.5, P1:IC10.8, P1:J5.1, P1:J5.2, P1:OK5.6, P1:R43.1, P1:R48.2, P1:R49.2, PW:C23.1, PW:IC2*4.3, PW:L5.2, PW:R20.2
VCC10: DC5.4, P2:C22.1, P2:C23.1, P2:C24.+, P2:C25.+, P2:IC9.5, P2:IC10.8, P2:OK5.6, P2:R43.1, P2:R48.2, P2:R49.2
VCC11: DC6.2, P1:C27.1, P1:C28.1, P1:C29.+, P1:C30.+, P1:IC11.5, P1:IC12.8, P1:J6.1, P1:J6.2, P1:OK6.6, P1:R53.1, P1:R58.2, P1:R59.2, PW:C28.1, PW:IC2*5.3, PW:L6.2, PW:R24.2
VCC12: DC6.4, P2:C27.1, P2:C28.1, P2:C29.+, P2:C30.+, P2:IC11.5, P2:IC12.8, P2:OK6.6, P2:R53.1, P2:R58.2, P2:R59.2
VCC13: DC7.2, P1:C32.1, P1:C33.1, P1:C34.+, P1:C35.+, P1:IC13.5, P1:IC14.8, P1:J7.1, P1:J7.2, P1:OK7.6, P1:R63.1, P1:R68.2, P1:R69.2, PW:C33.1, PW:IC2*6.3, PW:L7.2, PW:R28.2
VCC14: DC7.4, P2:C32.1, P2:C33.1, P2:C34.+, P2:C35.+, P2:IC13.5, P2:IC14.8, P2:OK7.6, P2:R63.1, P2:R68.2, P2:R69.2
VCC15: DC8.2, P1:C37.1, P1:C38.1, P1:C39.+, P1:C40.+, P1:IC15.5, P1:IC16.8, P1:J8.1, P1:J8.2, P1:OK8.6, P1:R73.1, P1:R78.2, P1:R79.2, PW:C38.1, PW:IC2*7.3, PW:L8.2, PW:R32.2
VCC16: DC8.4, P2:C37.1, P2:C38.1, P2:C39.+, P2:C40.+, P2:IC15.5, P2:IC16.8, P2:OK8.6, P2:R73.1, P2:R78.2, P2:R79.2

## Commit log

2018-02-01 inicializavimas
